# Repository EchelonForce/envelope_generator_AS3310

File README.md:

# Eurorack Envelope Generator AS3310 

This is a design for a Eurorack Envelope Generator based on the AS3310.

Full write up: https://www.robotdialogs.com/2023/01/eurorack-envelope-generator-adsr-as3310.html

This work is licensed under a Creative Commons Attribution-NonCommercial-ShareAlike 4.0 International License. https://creativecommons.org/licenses/by-nc-sa/4.0/

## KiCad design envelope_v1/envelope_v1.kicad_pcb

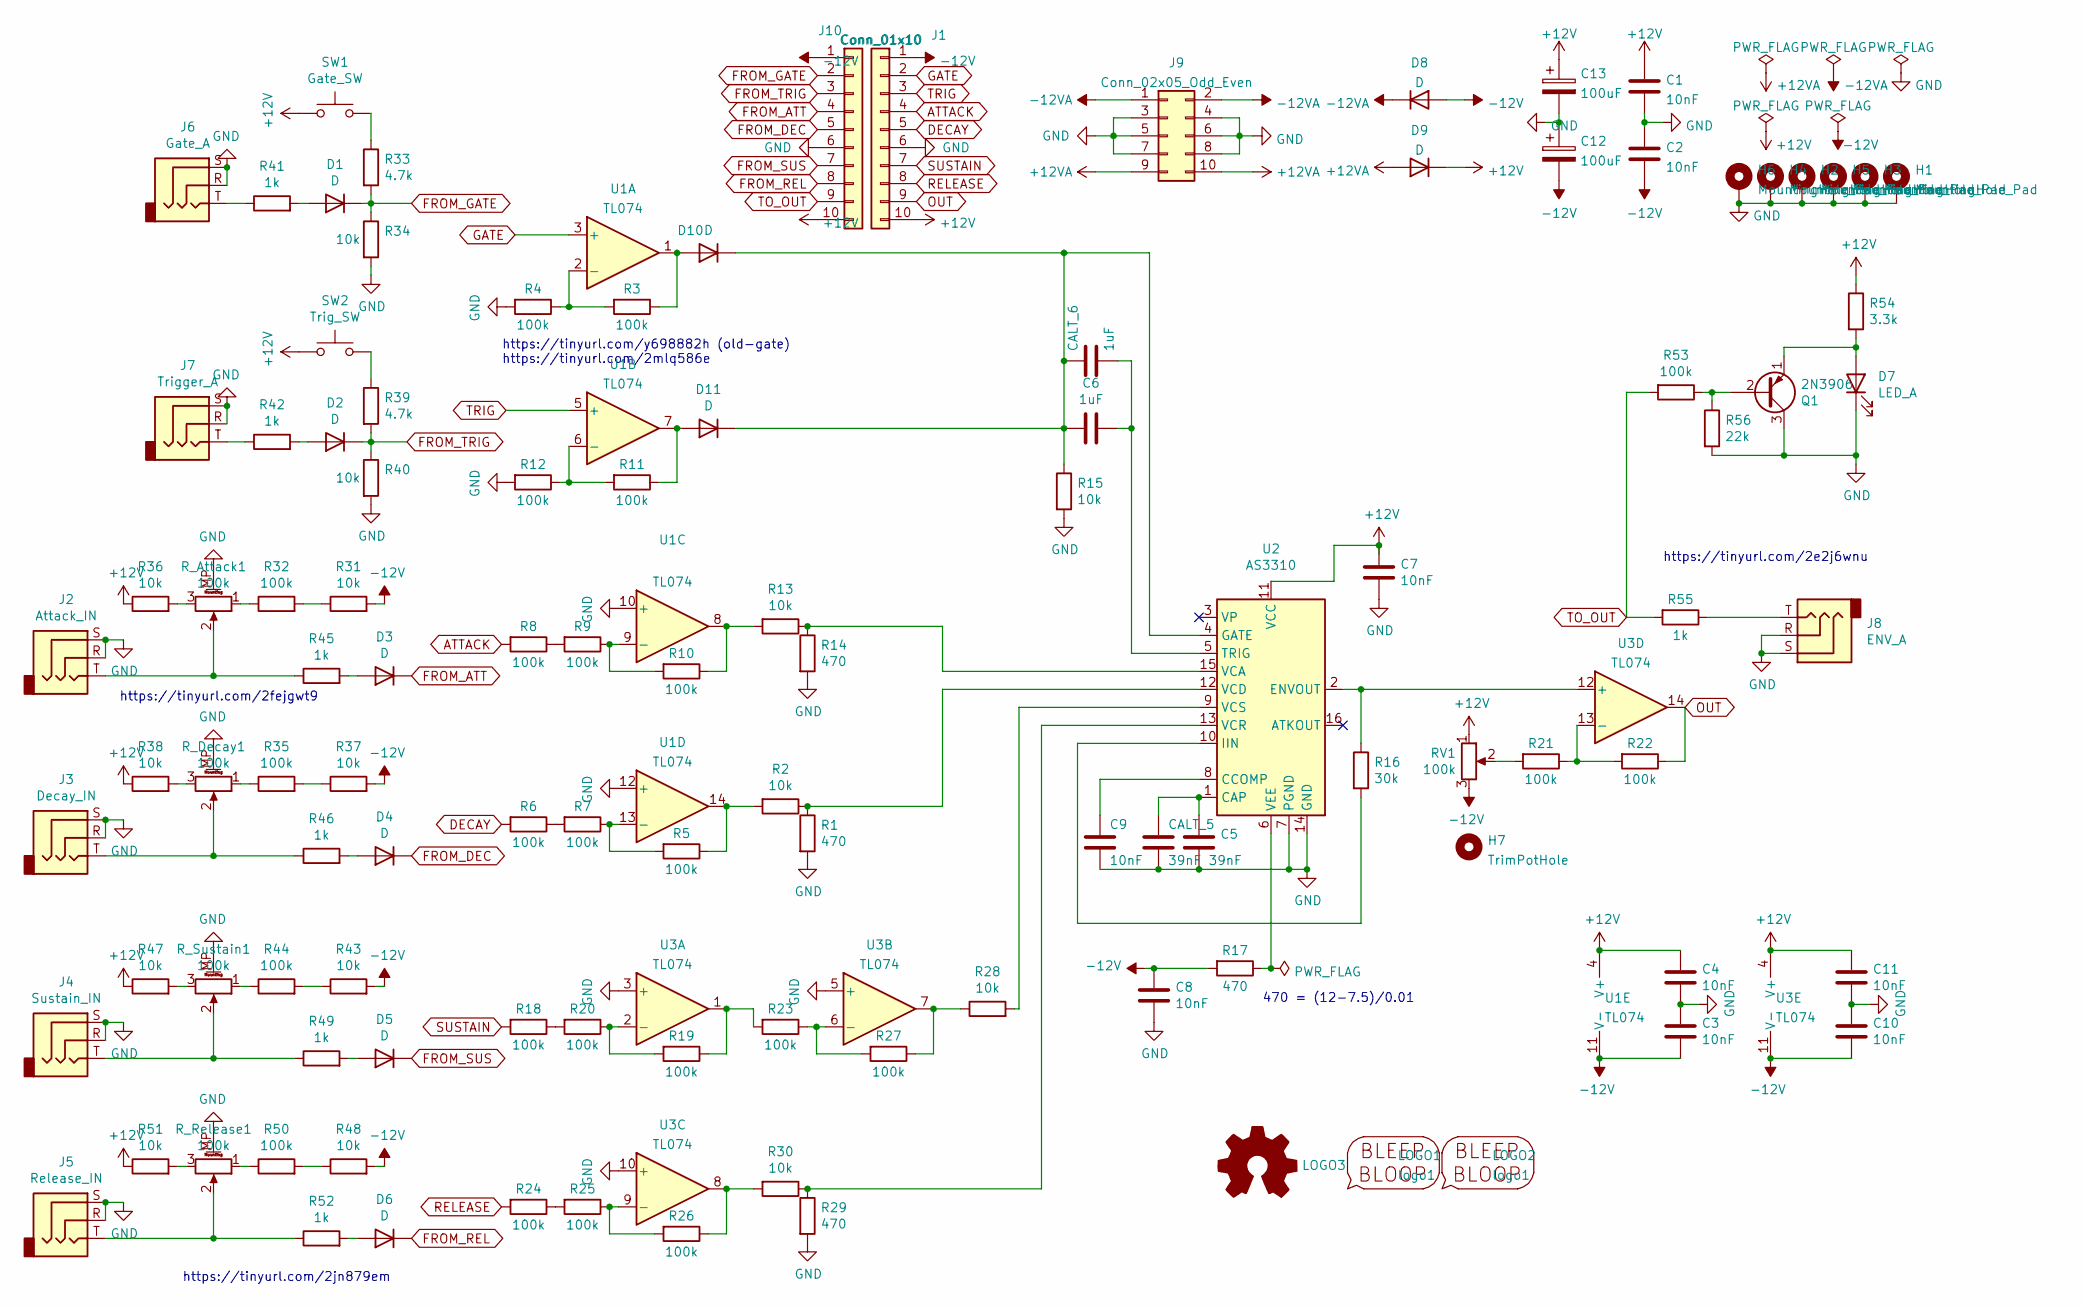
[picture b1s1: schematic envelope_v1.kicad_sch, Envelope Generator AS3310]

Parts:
C1, C2, C3, C4, C7, C8, C9, C10, C11: 10nF; C_1206_3216Metric_Pad1.33x1.80mm_HandSolder
C5: 39nF; C_1206_3216Metric_Pad1.33x1.80mm_HandSolder
C6: 1uF; C_1206_3216Metric_Pad1.33x1.80mm_HandSolder
C12, C13: 100uF; CP_Radial_D5.0mm_P2.50mm
CALT_5: 39nF; C_Disc_D5.1mm_W3.2mm_P5.00mm
CALT_6: 1uF; C_Disc_D5.1mm_W3.2mm_P5.00mm
D1, D2, D3, D4, D5, D6, D10, D11: D; D_DO-34_SOD68_P7.62mm_Horizontal
D7: LED_A; LED_D3.0mm
D8, D9: D; D_DO-41_SOD81_P10.16mm_Horizontal
H1, H2, H3, H4, H5, H6: MountingHole_Pad; MountingHole_3.2mm_M3_ISO7380_Pad_TopBottom
H7: TrimPotHole; MountingHole_4.3mm_M4_ISO14580
J1: Conn_01x10; PinSocket_1x10_P2.54mm_Vertical
J2: Attack_IN; Jack_3.5mm_MJ-355W_Vertical
J3: Decay_IN; Jack_3.5mm_MJ-355W_Vertical
J4: Sustain_IN; Jack_3.5mm_MJ-355W_Vertical
J5: Release_IN; Jack_3.5mm_MJ-355W_Vertical
J6: Gate_A; Jack_3.5mm_MJ-355W_Vertical
J7: Trigger_A; Jack_3.5mm_MJ-355W_Vertical
J8: ENV_A; Jack_3.5mm_MJ-355W_Vertical
J9: Conn_02x05_Odd_Even; IDC-Header_2x05_P2.54mm_Vertical
J10: Conn_01x10; PinHeader_1x10_P2.54mm_Vertical
LOGO1: logo1; Logo1
LOGO2: logo1; Logo2
LOGO3: Logo_Open_Hardware_Small; OSHW-Symbol_6.7x6mm_SilkScreen
Q1: 2N3906; TO-92_Inline_Wide
R1, R14, R17, R29: 470; R_1206_3216Metric_Pad1.30x1.75mm_HandSolder
R2, R13, R15, R28, R30, R31, R34, R36, R37, R38, R40, R43, R47, R48, R51: 10k; R_1206_3216Metric_Pad1.30x1.75mm_HandSolder
R3, R4, R5, R6, R7, R8, R9, R10, R11, R12, R18, R19, R20, R21, R22, R23, R24, R25, R26, R27, R32, R35, R44, R50, R53: 100k; R_1206_3216Metric_Pad1.30x1.75mm_HandSolder
R16: 30k; R_1206_3216Metric_Pad1.30x1.75mm_HandSolder
R33, R39: 4.7k; R_1206_3216Metric_Pad1.30x1.75mm_HandSolder
R41, R42, R45, R46, R49, R52, R55: 1k; R_1206_3216Metric_Pad1.30x1.75mm_HandSolder
R54: 3.3k; R_1206_3216Metric_Pad1.30x1.75mm_HandSolder
R56: 22k; R_1206_3216Metric_Pad1.30x1.75mm_HandSolder
RV1: 100k; Potentiometer_Bourns_3296W_Vertical
R_Attack1: 100k; Potentiometer_Alpha_RD901F-40-00D_Single_Vertical_w_3d
R_Decay1: 100k; Potentiometer_Alpha_RD901F-40-00D_Single_Vertical_w_3d
R_Release1: 100k; Potentiometer_Alpha_RD901F-40-00D_Single_Vertical_w_3d
R_Sustain1: 100k; Potentiometer_Alpha_RD901F-40-00D_Single_Vertical_w_3d
SW1: Gate_SW; SW_PS1024ALRED
SW2: Trig_SW; SW_PS1024ALRED
U1, U3: TL074; DIP-14_W7.62mm_Socket_LongPads
U2: AS3310; DIP-16_W7.62mm_Socket_LongPads

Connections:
+12V: C1.1, C4.2, C7.2, C11.2, C13.1, D9.1 (K), J1.10, J10.10, R36.1, R38.1, R47.1, R51.1, R54.1, RV1.1, SW1.1, SW2.1, U1.4 (V+), U2.11 (VCC), U3.4 (V+)
+12VA: D9.2 (A), J9.9, J9.10
-12V: C2.2, C3.1, C8.2, C10.1, C12.2, D8.2 (A), J1.1, J10.1, R17.2, R31.2, R37.2, R43.2, R48.2, RV1.3, U1.11 (V-), U3.11 (V-)
-12VA: D8.1 (K), J9.1, J9.2
ATTACK: J1.4, R8.2
DECAY: J1.5, R6.2
FROM_ATT: D3.1 (K), J10.4
FROM_DEC: D4.1 (K), J10.5
FROM_GATE: D1.1 (K), J10.2, R33.2, R34.1
FROM_REL: D6.1 (K), J10.8
FROM_SUS: D5.1 (K), J10.7
FROM_TRIG: D2.1 (K), J10.3, R39.2, R40.1
GATE: J1.2, U1.3 (+)
GND: C1.2, C2.1, C3.2, C4.1, C5.2, C7.1, C8.1, C9.2, C10.2, C11.1, C12.1, C13.2, CALT_5.2, D7.1 (K), H1.1, H2.1, H3.1, H4.1, H5.1, H6.1, J1.6, J2.R, J2.S, J3.R, J3.S, J4.R, J4.S, J5.R, J5.S, J6.R, J6.S, J7.R, J7.S, J8.R, J8.S, J9.3, J9.4, J9.5, J9.6, J9.7, J9.8, J10.6, Q1.3 (C), R1.2, R4.2, R12.2, R14.2, R15.2, R29.2, R34.2, R40.2, R56.2, R_Attack1.MP (MountPin), R_Decay1.MP (MountPin), R_Release1.MP (MountPin), R_Sustain1.MP (MountPin), U1.10 (+), U1.12 (+), U2.7 (PGND), U2.14 (GND), U3.3 (+), U3.5 (+), U3.10 (+)
unnamed: C5.1, CALT_5.1, U2.1 (CAP)
unnamed: C6.1, CALT_6.1, D10.1 (K), D11.1 (K), R15.1, U2.4 (GATE)
unnamed: C6.2, CALT_6.2, U2.5 (TRIG)
unnamed: C9.1, U2.8 (CCOMP)
unnamed: D1.2 (A), R41.2
unnamed: D2.2 (A), R42.2
unnamed: D3.2 (A), R45.2
unnamed: D4.2 (A), R46.2
unnamed: D5.2 (A), R49.2
unnamed: D6.2 (A), R52.2
unnamed: D7.2 (A), Q1.1 (E), R54.2
unnamed: D10.2 (A), R3.1, U1.1
unnamed: D11.2 (A), R11.1, U1.7
unnamed: J2.T, R45.1, R_Attack1.2
unnamed: J3.T, R46.1, R_Decay1.2
unnamed: J4.T, R49.1, R_Sustain1.2
unnamed: J5.T, R52.1, R_Release1.2
unnamed: J6.T, R41.1
unnamed: J7.T, R42.1
unnamed: J8.T, R55.1
unnamed: Q1.2 (B), R53.1, R56.1
unnamed: R1.1, R2.1, U2.12 (VCD)
unnamed: R2.2, R5.1, U1.14
unnamed: R3.2, R4.1, U1.2 (-)
unnamed: R5.2, R7.1, U1.13 (-)
unnamed: R6.1, R7.2
unnamed: R8.1, R9.2
unnamed: R10.1, R13.2, U1.8
unnamed: R9.1, R10.2, U1.9 (-)
unnamed: R11.2, R12.1, U1.6 (-)
unnamed: R13.1, R14.1, U2.15 (VCA)
unnamed: R16.1, U2.2 (ENVOUT), U3.12 (+)
unnamed: R16.2, U2.10 (IIN)
unnamed: R17.1, U2.6 (VEE)
unnamed: R18.1, R20.2
unnamed: R19.1, R23.2, U3.1
unnamed: R19.2, R20.1, U3.2 (-)
unnamed: R21.1, R22.2, U3.13 (-)
unnamed: R21.2, RV1.2
unnamed: R23.1, R27.2, U3.6 (-)
unnamed: R24.1, R25.2
unnamed: R25.1, R26.2, U3.9 (-)
unnamed: R26.1, R30.2, U3.8
unnamed: R27.1, R28.1, U3.7
unnamed: R28.2, U2.9 (VCS)
unnamed: R29.1, R30.1, U2.13 (VCR)
unnamed: R31.1, R32.2
unnamed: R32.1, R_Attack1.1
unnamed: R33.1, SW1.2
unnamed: R35.1, R_Decay1.1
unnamed: R35.2, R37.1
unnamed: R36.2, R_Attack1.3
unnamed: R38.2, R_Decay1.3
unnamed: R39.1, SW2.2
unnamed: R43.1, R44.2
unnamed: R44.1, R_Sustain1.1
unnamed: R47.2, R_Sustain1.3
unnamed: R48.1, R50.2
unnamed: R50.1, R_Release1.1
unnamed: R51.2, R_Release1.3
OUT: J1.9, R22.1, U3.14
RELEASE: J1.8, R24.2
SUSTAIN: J1.7, R18.2
TO_OUT: J10.9, R53.2, R55.2
TRIG: J1.3, U1.5 (+)

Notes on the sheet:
https://tinyurl.com/y698882h (old-gate) https://tinyurl.com/2mlq586e
470 = (12-7.5)/0.01
https://tinyurl.com/2fejgwt9
https://tinyurl.com/2jn879em
https://tinyurl.com/2e2j6wnu

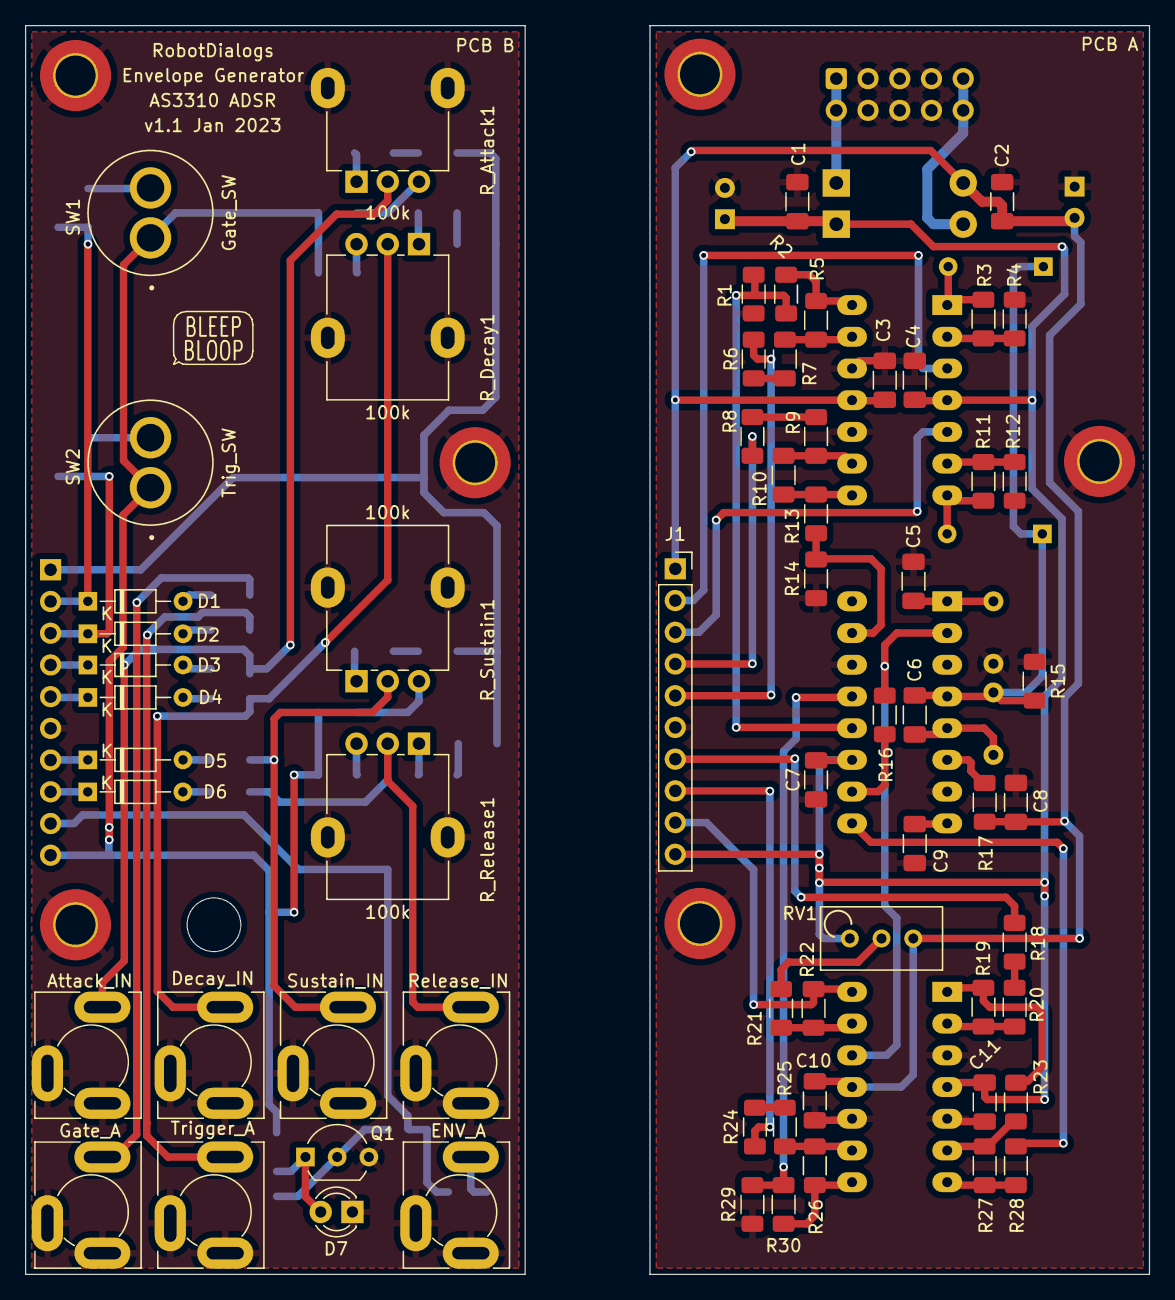
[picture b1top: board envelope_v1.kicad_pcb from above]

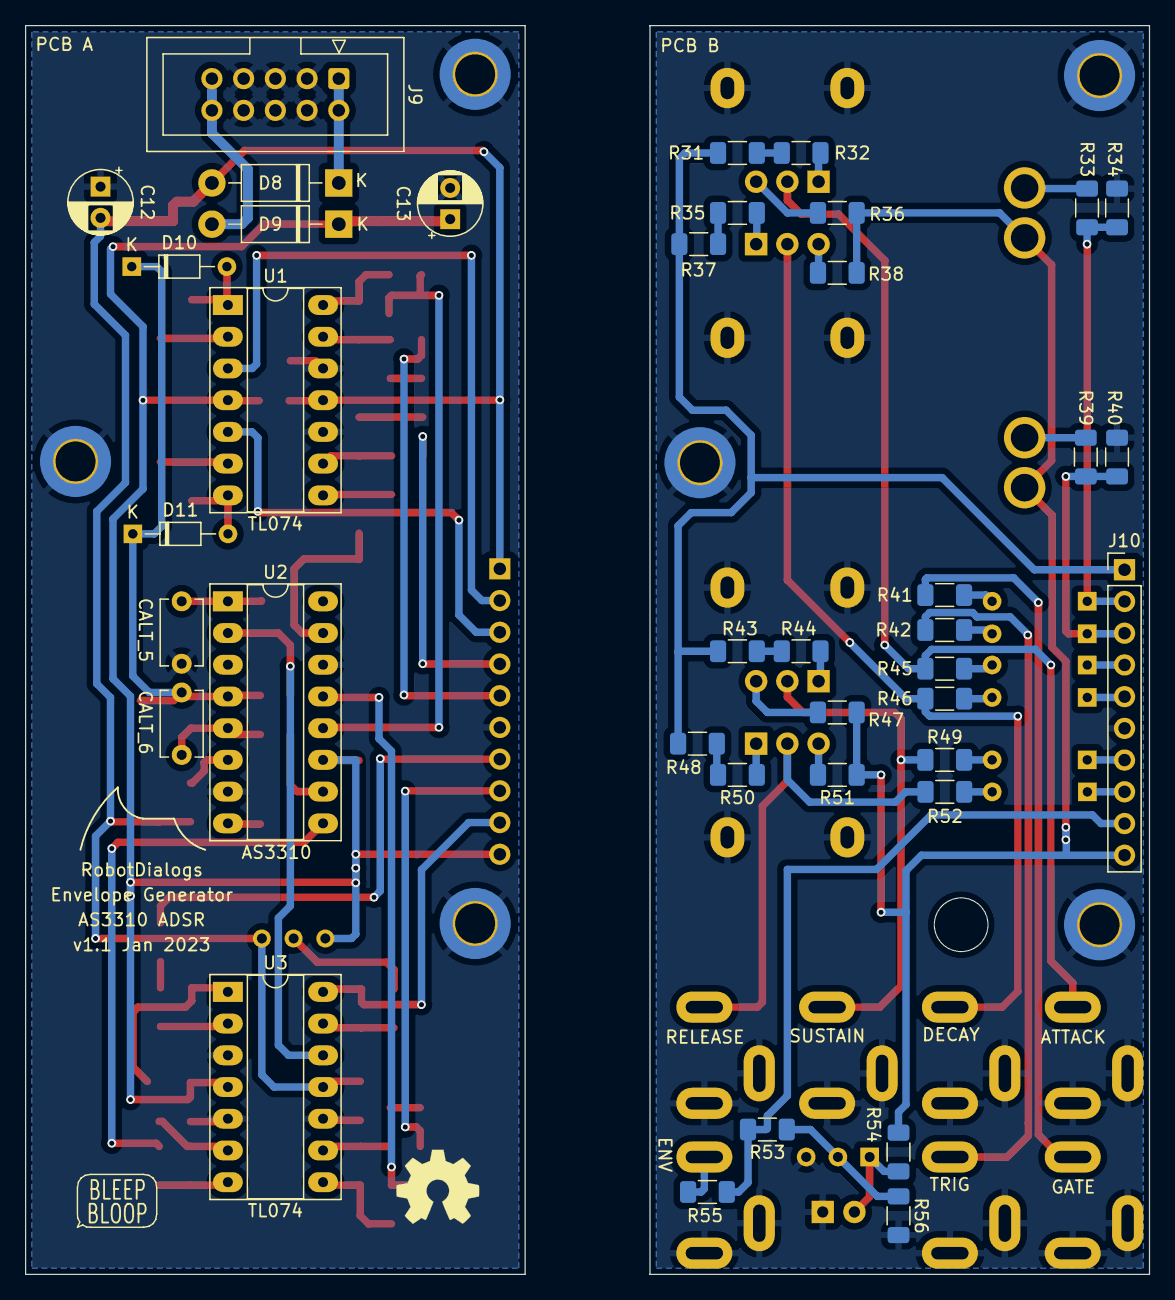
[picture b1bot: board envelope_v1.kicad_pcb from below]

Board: 2 copper layers, 90.0 x 100.0 mm, 113 parts (40 on the bottom side), 79 nets.

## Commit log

2022-12-07 Initial commit with .gitignore
2022-12-07 Notes and README
2022-12-07 Schematic and PCB draft
2022-12-07 Geographic re-annotate
2022-12-07 Cleanup and labels
2022-12-11 Panelized v1
2023-01-10 Front Panel v1 docs
2023-01-10 v1 redlines and Notes
2023-01-10 v1.1 fixes
2023-01-10 panelized v1.1
2023-01-19 Add v1.1 schematic pdf
